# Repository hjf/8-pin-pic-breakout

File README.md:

# 8-pin-pic-breakout
Breakout board for 8-pin Microchip PIC devices (10/12/16 family), for SMD and DIP.

## What is this?
This is a flexible breakout board for the 8-pin variants of PIC family devices. Most (all?) 8-pin PICs share the same pinout so it should be compatible with all of them. It has been designed with a PIC18F18313 in mind, but it should work perfectly with the classic PIC12F675. It's compatible with DIP and SOIC packages. Why would you need a breakout board for a DIP, you ask? Read on and you will find out!

## What's special about this breakout?
I designed this breakout to be as flexible as possible. It includes a few onboard components:
- **5-pin header for ICSP:** It's a programming header. The pinout is compatible with PICKit2, 3 and 4. You can solder an angled .1" pin header here.
- **0603-size decoupling capacitor:** You can (and should) solder a .1uF (100nF) capacitor in every VDD pin of every IC in your board. It's not only good practice, but most manufacturers specify it in the datasheet.
- **0805-size MCLR resistor at MCLR:** PICs have an active-low RESET input. This board lets you solder a 0805 resistor to keep MCLR tied to VDD. This may be optional. Older PICs require it. Some PICs allow to disable VDD altogether, and newer PICs have an internal resistor. So you need to check your datasheet.
- **0805-size resistors for PGC and PGD:** These resistors are in series with the PGC/ICSPCLK and PGD/ICSPDAT pins. They are not strictly necessary (you can short them) but sometimes it's good for extra protection. A compromise value is 47-100 ohms. But you can use a higher value for added piece of mind.
- **Extra row of VDD and GND:** You can connect other breakout boards here. It's always nice to have extra power pins to power other breakouts.

## How to use it
Well, there are several ways to use this board. 

### Standard breakout 
In this mode, the board is just a breakout board. You solder a 8pin SOIC PIC and that's it. You can then solder wires into the provided wire pads. You can also use a DIP PIC (weird flex but ok).

### Standard breakout with programming header
Based on the "Standard breakout" mode, solder a 5-pin angled connector. Now it makes a little more sense with a DIP package. Remember to solder R2 and R3!

### DIP programmer
Instead of soldering a PIC directly, solder a 8-pin socket and an angled connector. You can now easily program 8 pin DIPs with your PICKIT2-3-4. Remeber to solder in R2/R3 or bridge them.

### SOIC to DIP adapter
Solder a SOIC IC, and solder two 4-pin, .1" short-pin headers sticking out through the bottom, to the innermost pin headers. It can now act as an adapter for your breadboard. You can solder a programming header too. 

### Breadboard adapter
While SOIC to DIP works great, for breadboards it may make more sense to solder to the outermost headers, for added stability when using it in a breadboard.

### Full-blown development board
You can solder in a PIC and all headers. The headers can be male or female, or female with long pins (male on the bottom, good for sticking into breadboards, and female on the top for extra female pins). The same goes for the extra power connectors. Or you can use long-pin male headers. Or just short male headers. Or just female headers. You can customize it to whatever you need.

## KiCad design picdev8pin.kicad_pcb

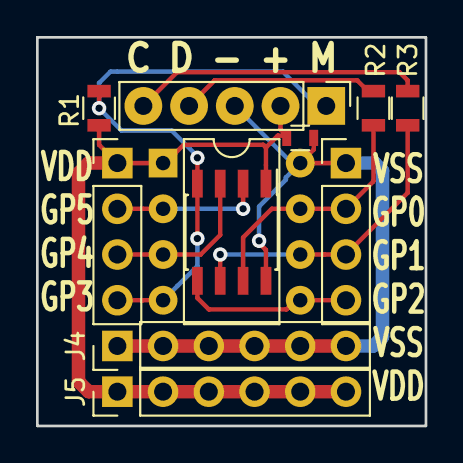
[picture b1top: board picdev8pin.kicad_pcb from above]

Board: 2 copper layers, 21.6 x 21.6 mm, 11 parts (0 on the bottom side), 10 nets.

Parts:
C1: C; R_0603
J1: Conn_01x05_Female; Pin_Header_Straight_1x05_Pitch2.54mm
J2, J3: Conn_01x04_Male; Pin_Header_Straight_1x04_Pitch2.54mm
J4, J5: Conn_01x06_Female; Pin_Header_Straight_1x06_Pitch2.54mm
R1, R2, R3: R; R_0805
U1: PIC12F675-IMC; SOIC-8_3.9x4.9mm_Pitch1.27mm
U2: PIC12F675-IMC; DIP-8_W7.62mm

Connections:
MCLR: J1.1, J3.4, R1.1, U1.4, U2.4
unnamed: J1.4, R2.1
unnamed: J1.5, R3.1
unnamed: J2.4, U1.5, U2.5
unnamed: J3.2, U1.2, U2.2
unnamed: J3.3, U1.3, U2.3
PGC: J2.3, R3.2, U1.6, U2.6
PGD: J2.2, R2.2, U1.7, U2.7
VDD: C1.1, J1.2, J3.1, J5.1, J5.2, J5.3, J5.4, J5.5, J5.6, R1.2, U1.1, U2.1
VSS: C1.2, J1.3, J2.1, J4.1, J4.2, J4.3, J4.4, J4.5, J4.6, U1.8, U2.8

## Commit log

2018-11-19 Kicad files
